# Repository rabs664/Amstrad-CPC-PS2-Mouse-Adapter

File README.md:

# Amstrad-CPC-PS2-Mouse-Adapter
This is a reproduction of Bryce's PS2 Mouse Adapter, see [CPC Wiki PS2 Mouse](https://www.cpcwiki.eu/index.php?title=PS2Mouse)

>[!NOTE]
>Acknowledgements go to Bryce for posting the origin design to the CPC Wiki. Many Thanks.

>[!CAUTION]
>USE AT YOUR OWN RISK.
>There is always the risk that the PS2 Mouse Adapter could cause harm to your CPC. Although I have tested the PS2 Mouse Adapter, there is no guarantee that it will work properly under all circumstances.

This repository contains my reproduction of the Bryce's PS2 Mouse Adapter and includes the KiCad 7.0 project files, gerber files and a 3D printable case. For all other information see [CPC Wiki PS2 Mouse](https://www.cpcwiki.eu/index.php?title=PS2Mouse)

>[!NOTE]
>I used a straight through DB9 Male to Female cable similar to the one below to connect the PS2 Mouse Adapter.
>
>
>
>Power was provided using a 5.5mmx2.1mm DC Power Splitter Cable similar to the one below.
>

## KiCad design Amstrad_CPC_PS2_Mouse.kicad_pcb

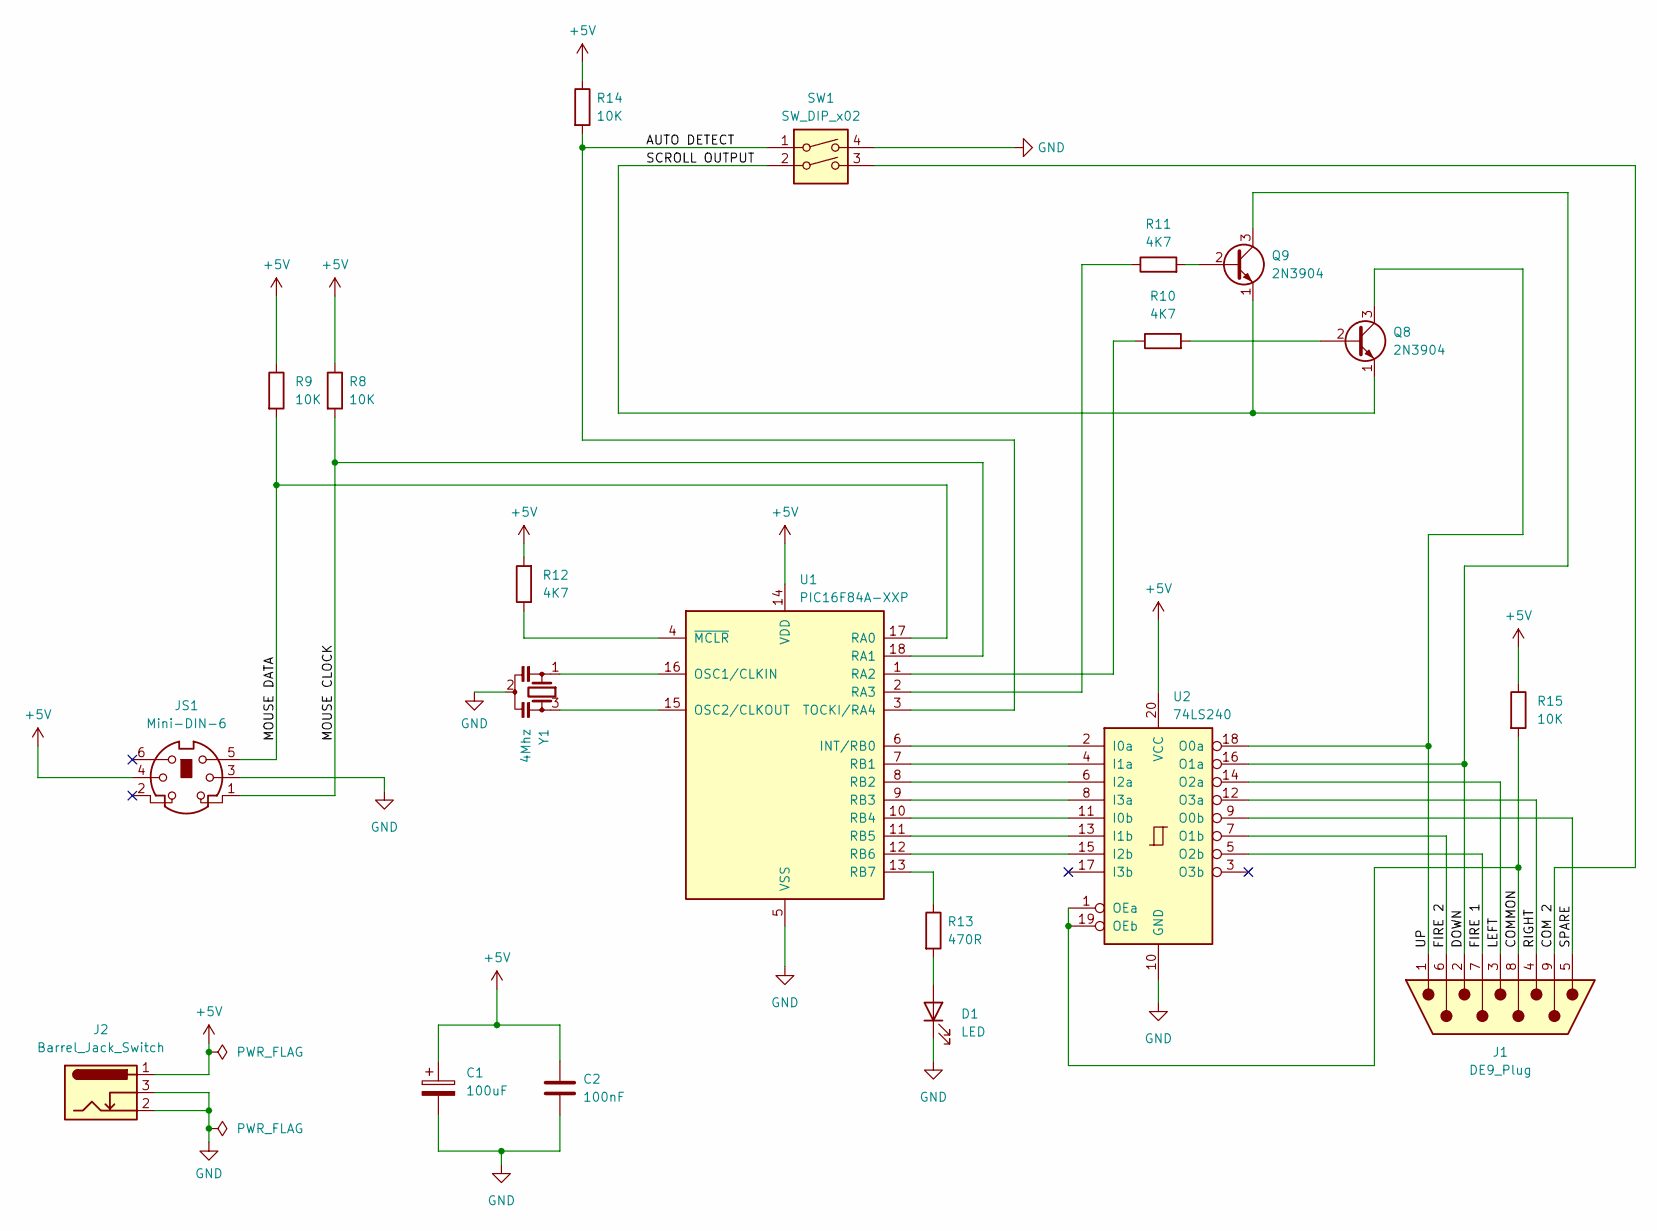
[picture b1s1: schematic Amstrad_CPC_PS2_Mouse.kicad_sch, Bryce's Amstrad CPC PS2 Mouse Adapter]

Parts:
C1: 100uF; CP_Radial_D6.3mm_P2.50mm
C2: 100nF; C_Disc_D5.0mm_W2.5mm_P5.00mm
D1: LED; LED_D1.8mm_W3.3mm_H2.4mm
J1: DE9_Plug; DSUB-9_Female_Horizontal_P2.77x2.84mm_EdgePinOffset7.70mm_H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
J2: Barrel_Jack_Switch; BarrelJack_Horizontal
JS1: Mini-DIN-6; Connector_Mini-DIN_Female_6Pin_2rows
Q8, Q9: 2N3904; TO-92_Inline
R8, R9, R14, R15: 10K; R_Axial_DIN0207_L6.3mm_D2.5mm_P10.16mm_Horizontal
R10, R11, R12: 4K7; R_Axial_DIN0207_L6.3mm_D2.5mm_P10.16mm_Horizontal
R13: 470R; R_Axial_DIN0207_L6.3mm_D2.5mm_P10.16mm_Horizontal
SW1: SW_DIP_x02; SW_DIP_SPSTx02_Slide_9.78x7.26mm_W7.62mm_P2.54mm
U1: PIC16F84A-XXP; DIP-18_W7.62mm_Socket_LongPads
U2: 74LS240; DIP-20_W7.62mm_Socket_LongPads
Y1: 4Mhz; Resonator-3Pin_W10.0mm_H5.0mm

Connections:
+5V: C1.1, C2.1, J2.1, JS1.4, R8.1, R9.1, R12.2, R14.1, R15.1, U1.14 (VDD), U2.20 (VCC)
/AUTO DETECT: R14.2, SW1.1, U1.3 (TOCKI/RA4)
/COM 2: J1.9, SW1.3
/COMMON: J1.8, R15.2, U2.1 (OEa), U2.19 (OEb)
/DOWN: J1.2, Q9.3 (C), U2.16 (O1a)
/FIRE 1: J1.7, U2.5 (O2b)
/FIRE 2: J1.6, U2.7 (O1b)
/LEFT: J1.3, U2.14 (O2a)
/MOUSE CLOCK: JS1.1, R8.2, U1.18 (RA1)
/MOUSE DATA: JS1.5, R9.2, U1.17 (RA0)
/RIGHT: J1.4, U2.12 (O3a)
/SCROLL OUTPUT: Q8.1 (E), Q9.1 (E), SW1.2
/SPARE: J1.5, U2.9 (O0b)
/UP: J1.1, Q8.3 (C), U2.18 (O0a)
GND: C1.2, C2.2, D1.1 (K), J2.2, J2.3, JS1.3, SW1.4, U1.5 (VSS), U2.10 (GND), Y1.2
unnamed: D1.2 (A), R13.2
unnamed: Q8.2 (B), R10.2
unnamed: Q9.2 (B), R11.2
unnamed: U1.6 (INT/RB0), U2.2 (I0a)
unnamed: U1.16 (OSC1/CLKIN), Y1.1
unnamed: U1.15 (OSC2/CLKOUT), Y1.3
unnamed: R10.1, U1.1 (RA2)
unnamed: R11.1, U1.2 (RA3)
unnamed: U1.7 (RB1), U2.4 (I1a)
unnamed: U1.8 (RB2), U2.6 (I2a)
unnamed: U1.9 (RB3), U2.8 (I3a)
unnamed: U1.10 (RB4), U2.11 (I0b)
unnamed: U1.11 (RB5), U2.13 (I1b)
unnamed: U1.12 (RB6), U2.15 (I2b)
unnamed: R13.1, U1.13 (RB7)
unnamed: R12.1, U1.4 (~MCLR)

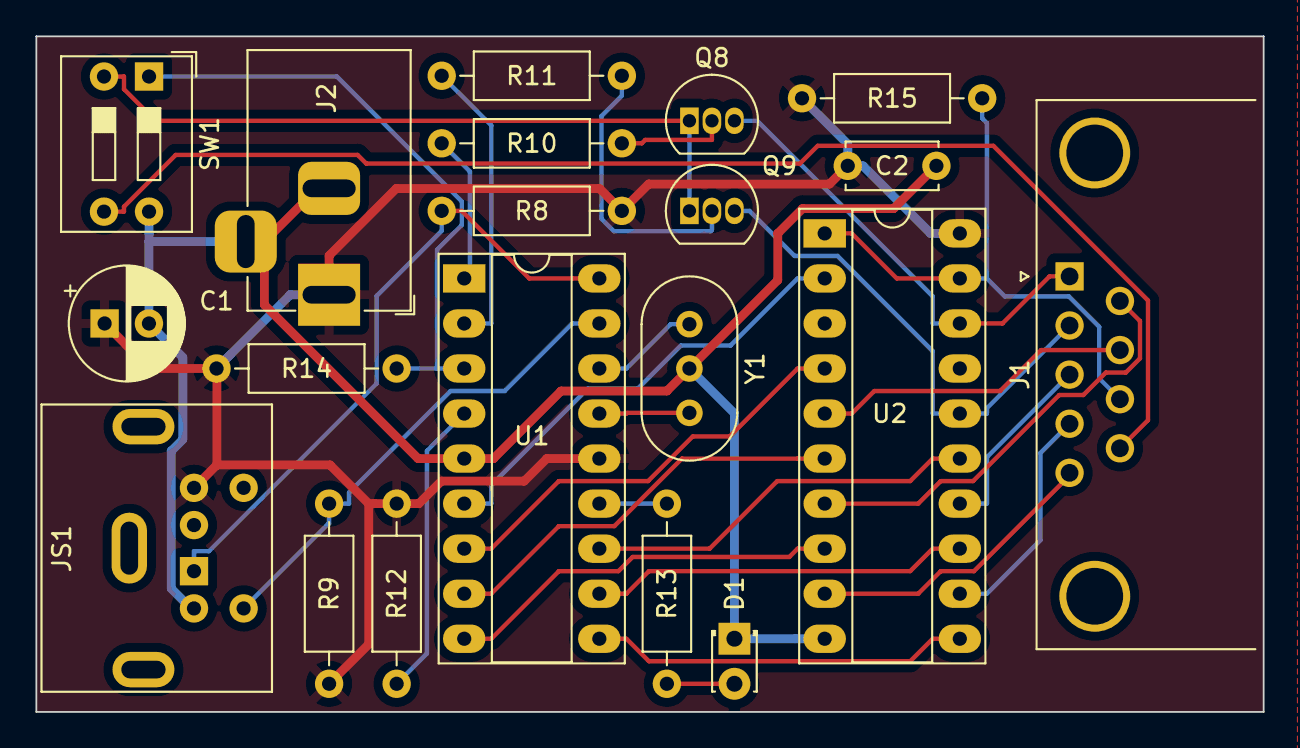
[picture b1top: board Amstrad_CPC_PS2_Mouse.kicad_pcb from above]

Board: 2 copper layers, 69.2 x 38.1 mm, 20 parts (0 on the bottom side), 31 nets.
